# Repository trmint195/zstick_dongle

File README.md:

# ZStick dongle

## 🔐 Setup 2.4G AES Encryption Key

To generate a random 128-bit AES Key for secure wireless communication and compile your firmware:

1. Go to the **Actions** tab in your GitHub repository.
2. In the left sidebar, select **Generate AES Key and Build**.
3. Click the **Run workflow** dropdown menu on the right.
4. Select your branch (e.g., `main`) and click **Run workflow**.

> **Note:** This action automatically scans all `.conf` files in the `config/` directory for `CONFIG_ZMK_2G4_AES_KEY`, updates them with a matching random 32-character hexadecimal key, commits the changes to your repository, and triggers the ZMK firmware build process immediately. Subsequent standard builds will reuse this generated key.

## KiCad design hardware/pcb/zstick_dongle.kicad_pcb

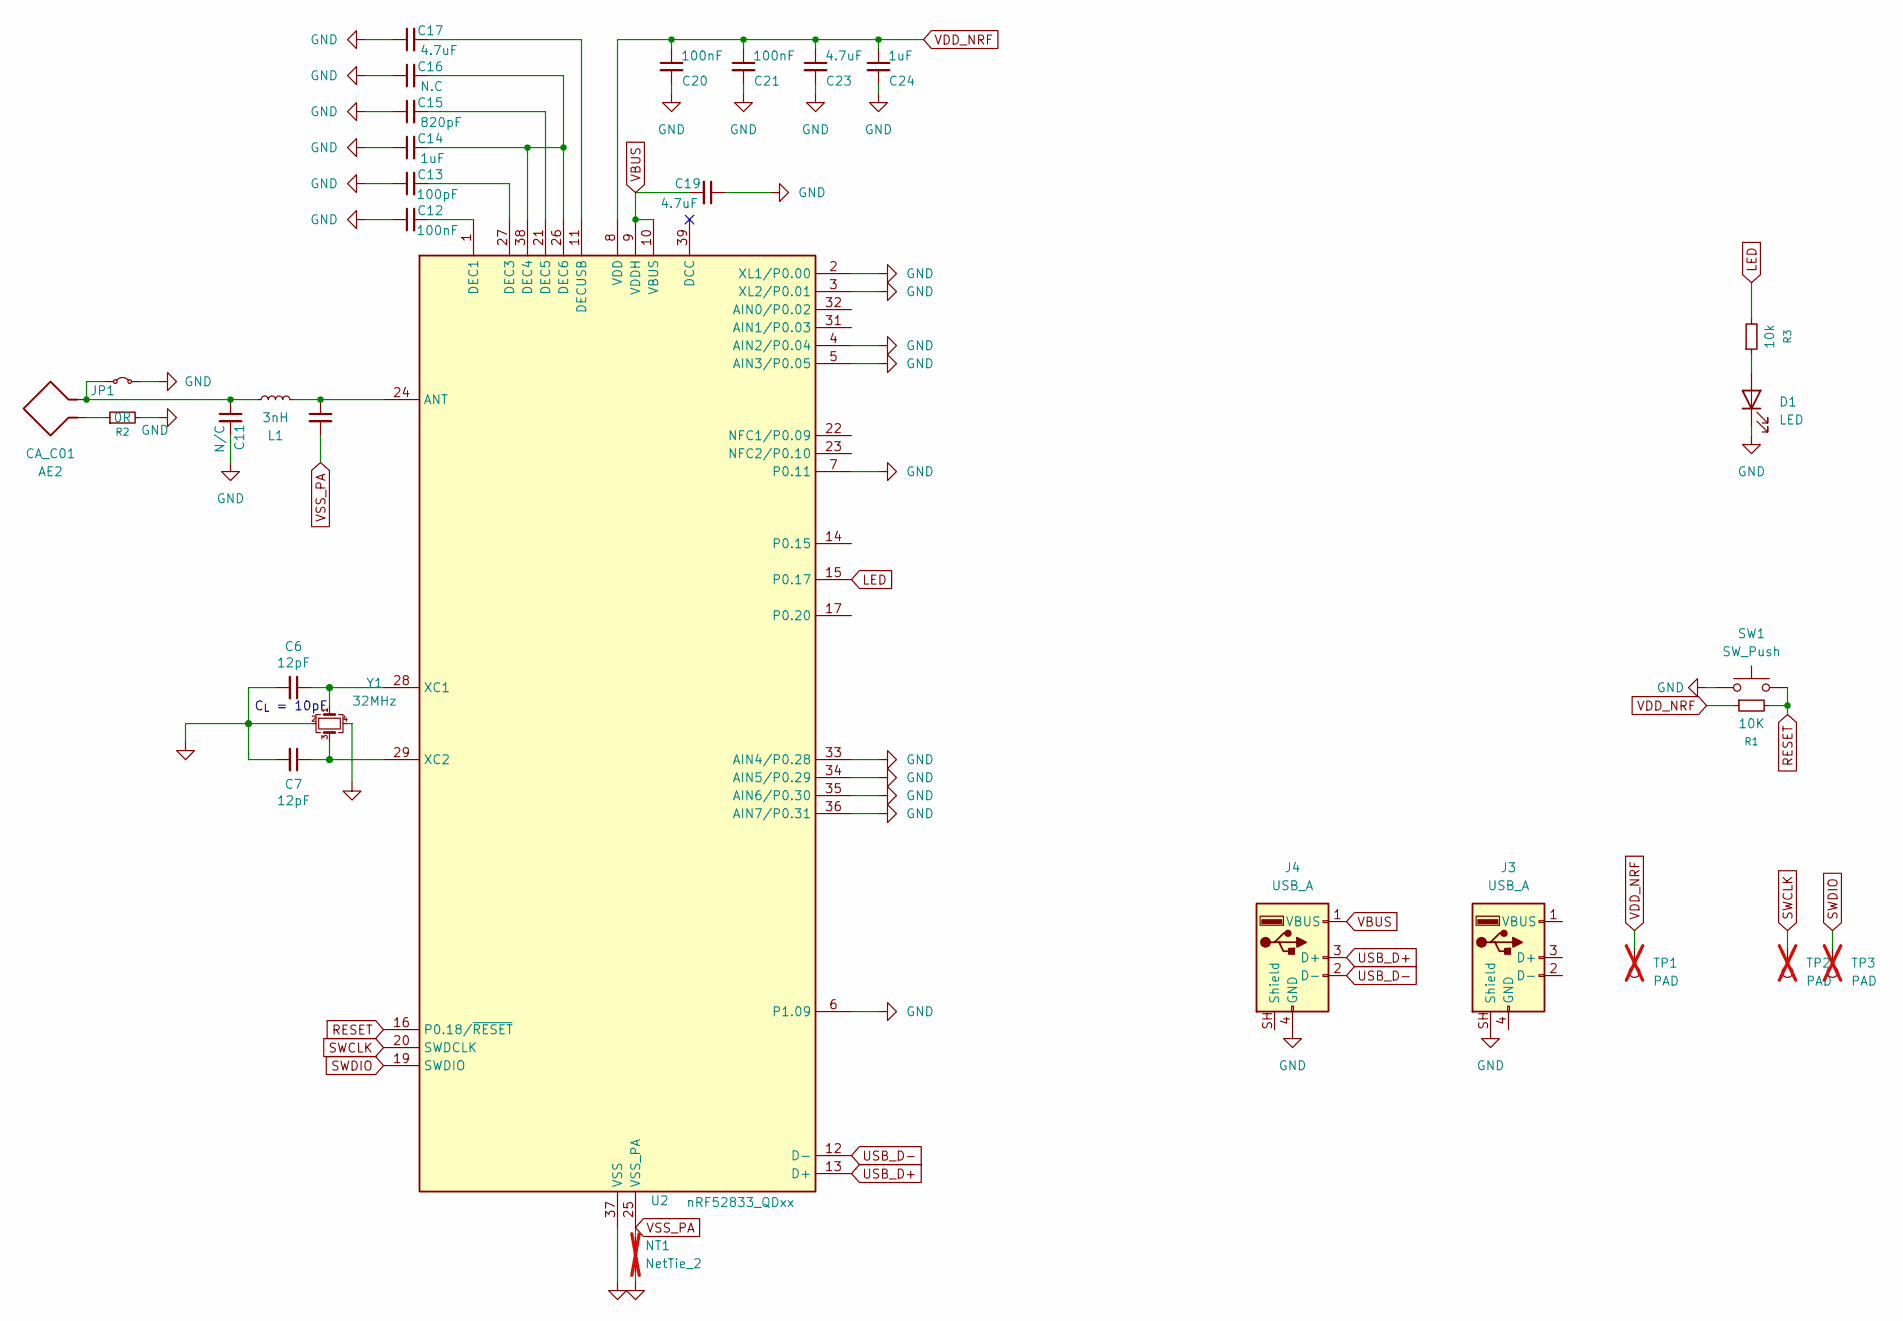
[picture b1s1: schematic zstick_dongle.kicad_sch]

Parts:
AE2: CA_C01; footprints__CA-C01_2a82fc1f67
C6, C7: 12pF; Capacitor_SMD__C_0402_1005Metric_c6f3790037; Manufacturer Part CL05C150JB51PNC; LCSC Part C1548
C8, C11: N/C; Capacitor_SMD__C_0402_1005Metric_c6f3790037
C12, C20, C21: 100nF; Capacitor_SMD__C_0402_1005Metric_c6f3790037
C13: 100pF; Capacitor_SMD__C_0402_1005Metric_c6f3790037
C14, C24: 1uF; Capacitor_SMD__C_0402_1005Metric_c6f3790037
C15: 820pF; Capacitor_SMD__C_0402_1005Metric_c6f3790037
C16: N.C; Capacitor_SMD__C_0402_1005Metric_c6f3790037
C17, C19, C23: 4.7uF; Capacitor_SMD__C_0402_1005Metric_c6f3790037
D1: LED; LED_SMD__LED_Kingbright_APA1606_1.6x0.6mm_Horizontal_45fcc6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
J3: USB_A; Connector_USB__USB_A_CNCTech_1001-011-01101_Horizontal_8752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
J4: USB_A; kien242__USB_A_PCB_Connect_c7ed2fe2dd
JP1: footprints__net-tie-2-tiny_d7e91cdf7c
L1: 3nH; Inductor_SMD__L_0402_1005Metric_527c86f58f
NT1: NetTie_2; footprints__net-tie-2-tiny-longer_cd91942636; not fitted
R1: 10K; Resistor_SMD__R_0402_1005Metric_a72d4a34ce
R2: 0R; Resistor_SMD__R_0402_1005Metric_a72d4a34ce
R3: 10k; Resistor_SMD__R_0402_1005Metric_a72d4a34ce
SW1: SW_Push; Button_Switch_SMD__SW_SPST_B3U-1000P_aba484aacf
TP1, TP2, TP3: PAD; TestPoint__TestPoint_Pad_D1.0mm_9a299b34f1; not fitted
U2: nRF52833_QDxx; Package_DFN_QFN__QFN-40-1EP_5x5mm_P0.4mm_EP3.6x3.6mm_7e83d5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
Y1: 32MHz; footprints__Crystal_SMD_2016-4Pin_2.0x1.6mm_13c9ed40cb; Manufacturer Part Q22FA1280001800; LCSC Part C255896

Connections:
GND: C6.2, C7.2, C11.2, C12.1, C13.1, C14.1, C15.1, C16.1, C17.1, C19.1, C20.2, C21.2, C23.2, C24.2, D1.1 (K), J3.SH (Shield_SH), J4.4 (GND), JP1.2 (B), NT1.2, R2.2, SW1.1, U2.2 (XL1/P0.00), U2.3 (XL2/P0.01), U2.4 (AIN2/P0.04), U2.5 (AIN3/P0.05), U2.6 (P1.09), U2.7 (P0.11), U2.33 (AIN4/P0.28), U2.34 (AIN5/P0.29), U2.35 (AIN6/P0.30), U2.36 (AIN7/P0.31), U2.37 (VSS), U2.41 (VSS), Y1.2, Y1.4
LED: R3.2, U2.15 (P0.17)
unnamed: AE2.2, R2.1
unnamed: D1.2 (A), R3.1
unnamed: AE2.1, C11.1, JP1.1 (A), L1.2
unnamed: C8.1, L1.1, U2.24 (ANT)
unnamed: C12.2, U2.1 (DEC1)
unnamed: C13.2, U2.27 (DEC3)
unnamed: C14.2, C16.2, U2.26 (DEC6), U2.38 (DEC4)
unnamed: C15.2, U2.21 (DEC5)
unnamed: C17.2, U2.11 (DECUSB)
unnamed: C6.1, U2.28 (XC1), Y1.1
unnamed: C7.1, U2.29 (XC2), Y1.3
RESET: R1.2, SW1.2, U2.16 (P0.18/~RESET)
SWCLK: TP2.1 (1_1), U2.20 (SWDCLK)
SWDIO: TP3.1 (1_1), U2.19 (SWDIO)
USB_D+: J4.3 (D+), U2.13 (D+)
USB_D-: J4.2 (D-), U2.12 (D-)
VBUS: C19.2, J4.1 (VBUS), U2.9 (VDDH), U2.10 (VBUS)
VDD_NRF: C20.1, C21.1, C23.1, C24.1, R1.1, TP1.1 (1_1), U2.8 (VDD), U2.18 (VDD), U2.30 (VDD), U2.40 (VDD)
VSS_PA: C8.2, NT1.1, U2.25 (VSS_PA)

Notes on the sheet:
C_{L} = 10pF

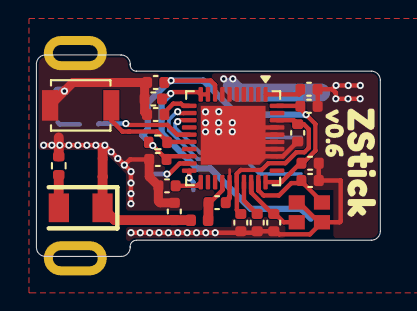
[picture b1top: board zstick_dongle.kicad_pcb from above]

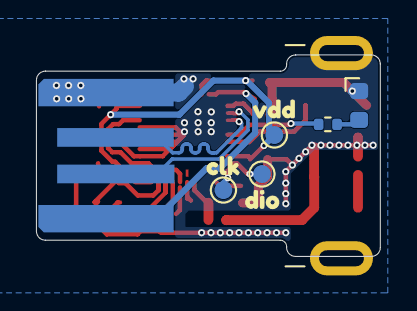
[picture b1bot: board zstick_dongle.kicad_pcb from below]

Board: 2 copper layers, 19.1 x 11.2 mm, 36 parts (10 on the bottom side), 21 nets.

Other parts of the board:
kibuzzard-6AE2EDA1: G***; kibuzzard-6AE2EDA1
kibuzzard-6AE2EDD1: G***; kibuzzard-6AE2EDD1
kibuzzard-6AE346F4: G***; kibuzzard-6AE346F4
kibuzzard-6AE3471E: G***; kibuzzard-6AE3471E
kibuzzard-6AE34710: G***; kibuzzard-6AE34710

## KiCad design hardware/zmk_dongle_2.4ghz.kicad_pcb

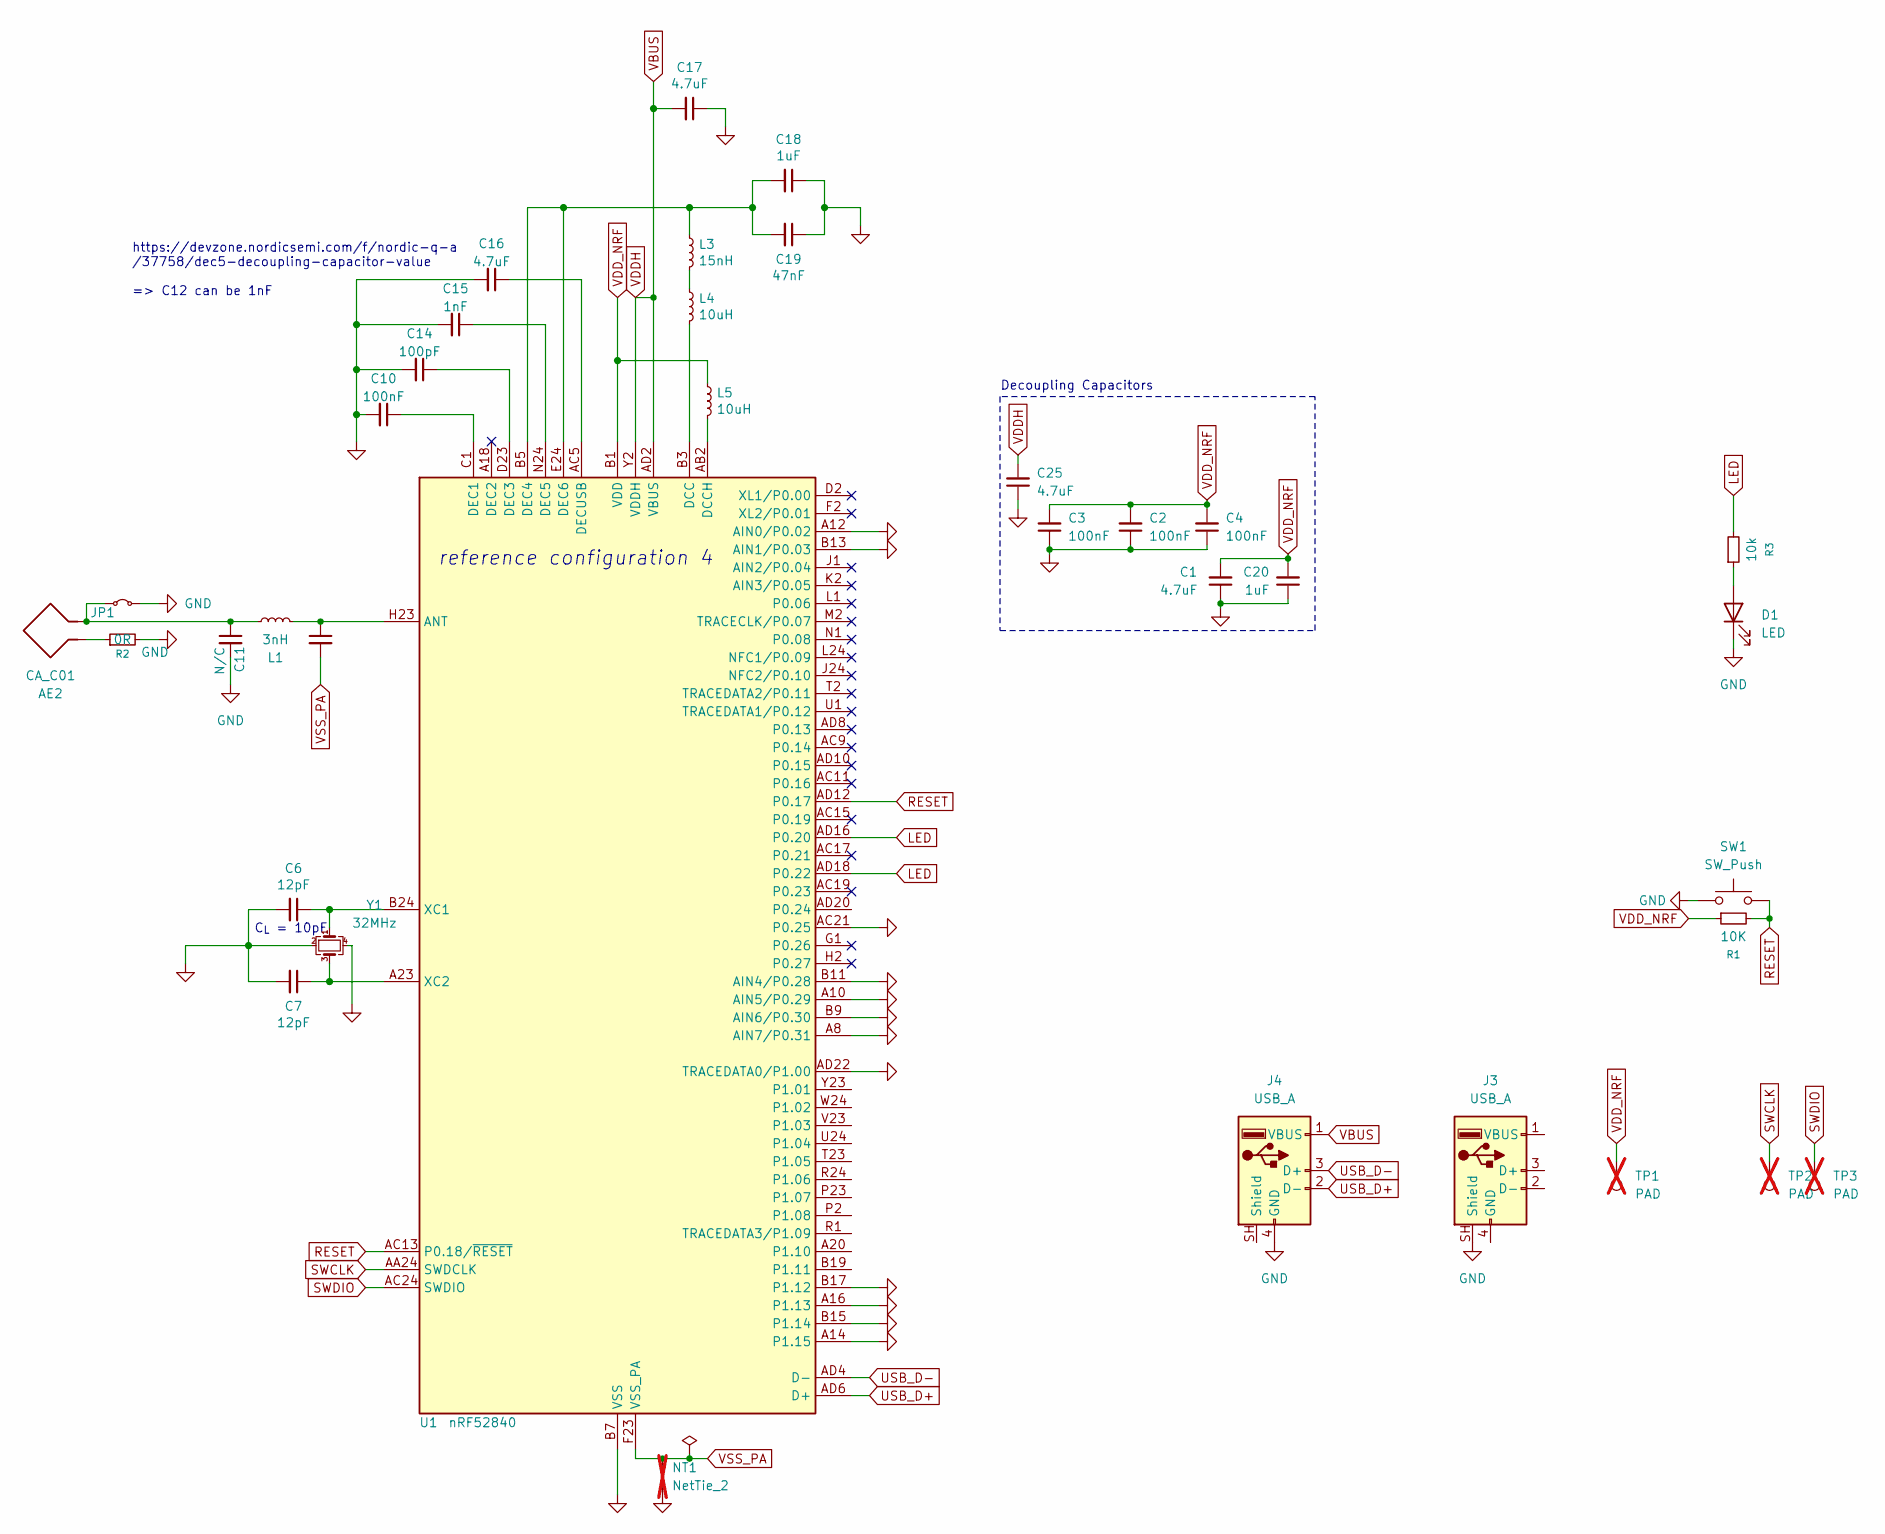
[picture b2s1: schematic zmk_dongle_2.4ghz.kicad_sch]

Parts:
AE2: CA_C01; CA-C01
C1, C16, C17, C25: 4.7uF; C_0402_1005Metric; Manufacturer Part CL05A475KP5NRNC; LCSC Part C368809
C2, C3, C4, C10: 100nF; C_0402_1005Metric; Manufacturer Part CL05B104KA5NNNC; LCSC Part C307331
C6, C7: 12pF; C_0402_1005Metric; Manufacturer Part CL05C150JB51PNC; LCSC Part C1548
C8, C11: N/C; C_0402_1005Metric
C14: 100pF; C_0402_1005Metric; Manufacturer Part CL05C101JB5NNNC; LCSC Part C1546
C15: 1nF; C_0402_1005Metric; Manufacturer Part CL05B102KB5NNNC; LCSC Part C1523
C18, C20: 1uF; C_0402_1005Metric; Manufacturer Part CL05A105KO5NNNC; LCSC Part C52923
C19: 47nF; C_0402_1005Metric; Manufacturer Part CL05B473KO5NNNC; LCSC Part C726525
D1: LED; LED_Kingbright_APA1606_1.6x0.6mm_Horizontal
J3: USB_A; USB_A_CNCTech_1001-011-01101_Horizontal
J4: USB_A; USB_A_PCB_Connect
JP1: net-tie-2-tiny
L1: 3nH; L_0402_1005Metric
L3: 15nH; L_0402_1005Metric; Manufacturer Part MLG1005S15NJT000; LCSC Part C27143
L4, L5: 10uH; Inductor_0603_1608M-nosilk; Manufacturer Part MLF1608E100KTD00; LCSC Part C1035
NT1: NetTie_2; net-tie-2-tiny-longer; not fitted
R1: 10K; R_0402_1005Metric
R2: 0R; R_0402_1005Metric
R3: 10k; R_0402_1005Metric
SW1: SW_Push; SW_SPST_B3U-1000P
TP1, TP2, TP3: PAD; TestPoint_Pad_D1.0mm; not fitted
U1: nRF52840; AQFN-73-1EP_7x7mm_P0.5mm_NRF52840-custom; Manufacturer Part NRF52840-QIAA-R; LCSC Part C190794
Y1: 32MHz; Crystal_SMD_2016-4Pin_2.0x1.6mm; Manufacturer Part Q22FA1280001800; LCSC Part C255896

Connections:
GND: C1.1, C2.1, C3.1, C4.1, C6.2, C7.2, C10.2, C11.2, C14.2, C15.2, C16.2, C17.1, C18.1, C19.1, C20.1, C25.1, D1.1 (K), J3.SH (Shield_SH), J4.4 (GND), JP1.2 (B), NT1.2, R2.2, SW1.1, U1.A8 (AIN7/P0.31), U1.A10 (AIN5/P0.29), U1.A12 (AIN0/P0.02), U1.A14 (P1.15), U1.A16 (P1.13), U1.AC21 (P0.25), U1.AD22 (TRACEDATA0/P1.00), U1.B7 (VSS), U1.B9 (AIN6/P0.30), U1.B11 (AIN4/P0.28), U1.B13 (AIN1/P0.03), U1.B15 (P1.14), U1.B17 (P1.12), U1.EP (VSS), Y1.2, Y1.4
LED: R3.2, U1.AD16 (P0.20), U1.AD18 (P0.22)
unnamed: AE2.2, R2.1
unnamed: D1.2 (A), R3.1
unnamed: AE2.1, C11.1, JP1.1 (A), L1.2
unnamed: L3.2, L4.1
unnamed: C8.1, L1.1, U1.H23 (ANT)
unnamed: L4.2, U1.B3 (DCC)
unnamed: L5.2, U1.AB2 (DCCH)
unnamed: C10.1, U1.C1 (DEC1)
unnamed: C14.1, U1.D23 (DEC3)
unnamed: C18.2, C19.2, L3.1, U1.B5 (DEC4), U1.E24 (DEC6)
unnamed: C15.1, U1.N24 (DEC5)
unnamed: C16.1, U1.AC5 (DECUSB)
unnamed: C6.1, U1.B24 (XC1), Y1.1
unnamed: C7.1, U1.A23 (XC2), Y1.3
RESET: R1.2, SW1.2, U1.AC13 (P0.18/~RESET), U1.AD12 (P0.17)
SWCLK: TP2.1 (1_1), U1.AA24 (SWDCLK)
SWDIO: TP3.1 (1_1), U1.AC24 (SWDIO)
USB_D+: J4.2 (D-), U1.AD6 (D+)
USB_D-: J4.3 (D+), U1.AD4 (D-)
VBUS: C17.2, C25.2, J4.1 (VBUS), U1.AD2 (VBUS), U1.Y2 (VDDH)
VDD_NRF: C1.2, C2.2, C3.2, C4.2, C20.2, L5.1, R1.1, TP1.1 (1_1), U1.A22 (VDD), U1.AD14 (VDD), U1.AD23 (VDD), U1.B1 (VDD), U1.W1 (VDD)
VSS_PA: C8.2, NT1.1, U1.F23 (VSS_PA)

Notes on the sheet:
reference configuration 4
Decoupling Capacitors
C_{L} = 10pF
https://devzone.nordicsemi.com/f/nordic-q-a /37758/dec5-decoupling-capacitor-value => C12 can be 1nF

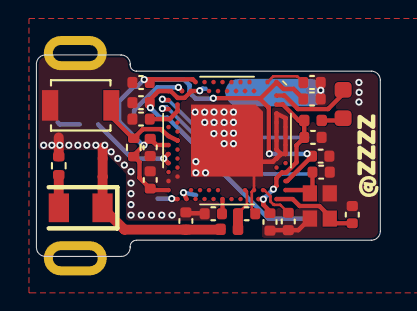
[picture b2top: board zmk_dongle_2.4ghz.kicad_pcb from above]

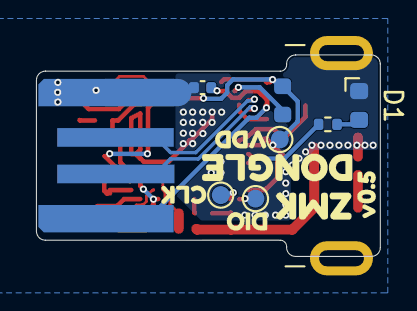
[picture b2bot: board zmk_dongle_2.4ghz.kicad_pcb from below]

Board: 2 copper layers, 19.1 x 11.2 mm, 43 parts (15 on the bottom side), 24 nets.

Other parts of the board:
kibuzzard-6AB69C4B: G***; kibuzzard-6AB69C4B
kibuzzard-6AB69C5E: G***; kibuzzard-6AB69C5E
kibuzzard-6AC6E950: G***; kibuzzard-6AC6E950
kibuzzard-6AC45A7D: G***; kibuzzard-6AC45A7D
kibuzzard-6AC65E3A: G***; kibuzzard-6AC65E3A
kibuzzard-6AC65E7A: G***; kibuzzard-6AC65E7A
kibuzzard-6AC65E65: G***; kibuzzard-6AC65E65
